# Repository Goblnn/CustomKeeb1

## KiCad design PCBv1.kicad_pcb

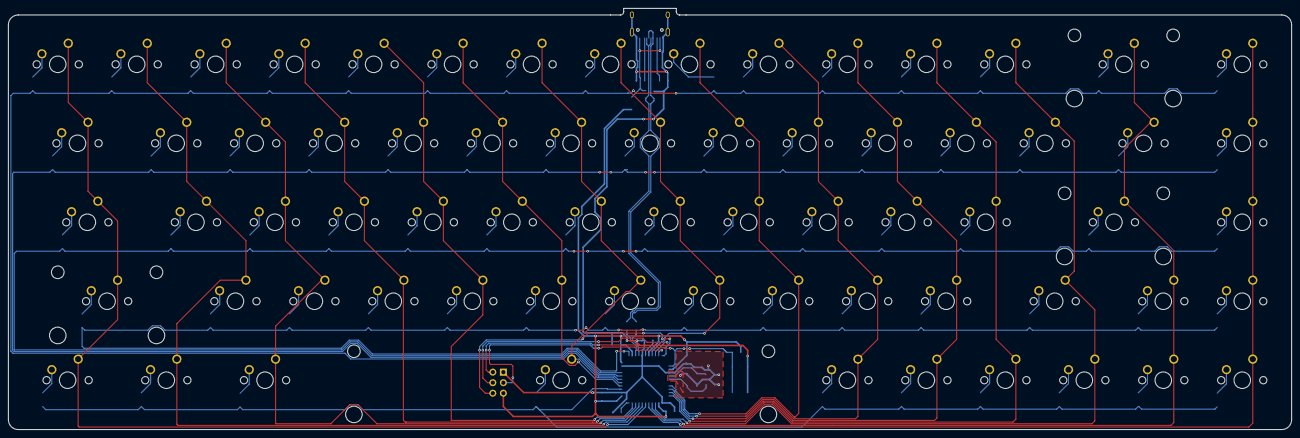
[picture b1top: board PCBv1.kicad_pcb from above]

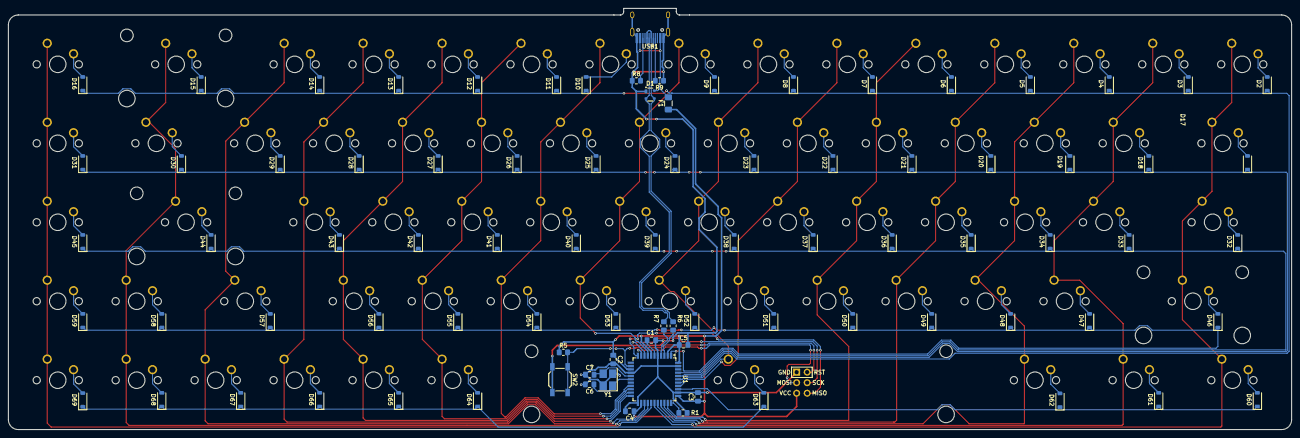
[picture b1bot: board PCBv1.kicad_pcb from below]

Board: 2 copper layers, 309.6 x 101.6 mm, 156 parts (88 on the bottom side), 105 nets.

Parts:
C1: 1uF; C_0805_2012Metric_Pad1.18x1.45mm_HandSolder
C2, C3, C4: 0.1uF; C_0805_2012Metric_Pad1.18x1.45mm_HandSolder
C5: 10uF; C_0805_2012Metric_Pad1.18x1.45mm_HandSolder
C6, C7: 22pF; C_0805_2012Metric_Pad1.18x1.45mm_HandSolder
D1: PRTR5V0U2X; SOT-143
D2, D3, D4, D5, D6, D7, D8, D9, D10, D11, D12, D13, D14, D15, D16, D17, D18, D19, D20, D21, D22, D23, D24, D25, D26, D27, D28, D29, D30, D31, D32, D33, D34, D35, D36, D37, D38, D39, D40, D41, D42, D43, D44, D45, D46, D47, D48, D49, D50, D51, D52, D53, D54, D55, D56, D57, D58, D59, D60, D61, D62, D63, D64, D65, D66, D67, D68, D69: D; D_SOD-123
F1: 500m; Fuse_1206_3216Metric_Pad1.42x1.75mm_HandSolder
J1: AVR-ISP-6; Reset_Pretty-Mask
R1, R5: 10k; R_0805_2012Metric_Pad1.20x1.40mm_HandSolder
R6, R7: 22; R_0805_2012Metric_Pad1.20x1.40mm_HandSolder
R8, R9: 5.1k; R_0805_2012Metric_Pad1.20x1.40mm_HandSolder
SW1: `~; MXOnly-1U-NoLED
SW2: SW_Push_Reset; SW_SPST_SKQG_WithStem
SW3: #1; MXOnly-1U-NoLED
SW4: #2; MXOnly-1U-NoLED
SW5: #3; MXOnly-1U-NoLED
SW6: #4; MXOnly-1U-NoLED
SW7: #5; MXOnly-1U-NoLED
SW8: #6; MXOnly-1U-NoLED
SW9: #7; MXOnly-1U-NoLED
SW10: #8; MXOnly-1U-NoLED
SW11: #9; MXOnly-1U-NoLED
SW12: #0; MXOnly-1U-NoLED
SW13: -_; MXOnly-1U-NoLED
SW14: =+; MXOnly-1U-NoLED
SW15: BSPC; MXOnly-2U-NoLED
SW16: PAUSE; MXOnly-1U-NoLED
SW17: TAB; MXOnly-1.5U-NoLED
SW18: Q; MXOnly-1U-NoLED
SW19: W; MXOnly-1U-NoLED
SW20: E; MXOnly-1U-NoLED
SW21: R; MXOnly-1U-NoLED
SW22: T; MXOnly-1U-NoLED
SW23: Y; MXOnly-1U-NoLED
SW24: U; MXOnly-1U-NoLED
SW25: I; MXOnly-1U-NoLED
SW26: O; MXOnly-1U-NoLED
SW27: P; MXOnly-1U-NoLED
SW28: [{; MXOnly-1U-NoLED
SW29: ]}; MXOnly-1U-NoLED
SW30: \|; MXOnly-1.5U-NoLED
SW31: NEXT; MXOnly-1U-NoLED
SW32: CPSLCK; MXOnly-1.75U-NoLED
SW33: A; MXOnly-1U-NoLED
SW34: S; MXOnly-1U-NoLED
SW35: D; MXOnly-1U-NoLED
SW36: F; MXOnly-1U-NoLED
SW37: G; MXOnly-1U-NoLED
SW38: H; MXOnly-1U-NoLED
SW39: J; MXOnly-1U-NoLED
SW40: K; MXOnly-1U-NoLED
SW41: L; MXOnly-1U-NoLED
SW42: ;:; MXOnly-1U-NoLED
SW43: '"; MXOnly-1U-NoLED
SW44: ENTR; MXOnly-2.25U-NoLED
SW45: PRVS; MXOnly-1U-NoLED
SW46: SHFT; MXOnly-2.25U-NoLED
SW47: Z; MXOnly-1U-NoLED
SW48: X; MXOnly-1U-NoLED
SW49: C; MXOnly-1U-NoLED
SW50: V; MXOnly-1U-NoLED
SW51: B; MXOnly-1U-NoLED
SW52: N; MXOnly-1U-NoLED
SW53: M; MXOnly-1U-NoLED
SW54: ,<; MXOnly-1U-NoLED
SW55: .>; MXOnly-1U-NoLED
SW56: /?; MXOnly-1U-NoLED
SW57: SHFT; MXOnly-1.75U-NoLED
SW58: UP; MXOnly-1U-NoLED
SW59: DEL; MXOnly-1U-NoLED
SW60: CTRL; MXOnly-1.25U-NoLED
SW61: WIN; MXOnly-1.25U-NoLED
SW62: ALT; MXOnly-1.25U-NoLED
SW63: SPC; MXOnly-6.25U-NoLED
SW64: ALT; MXOnly-1U-NoLED
SW65: FN; MXOnly-1U-NoLED
SW66: CTRL; MXOnly-1U-NoLED
SW67: LEFT; MXOnly-1U-NoLED
SW68: DOWN; MXOnly-1U-NoLED
SW69: RIGHT; MXOnly-1U-NoLED
U1: ATmega32U4-A; TQFP-44_10x10mm_P0.8mm
USB1: HRO-TYPE-C-31-M-12; HRO-TYPE-C-31-M-12-HandSoldering
Y1: 16MHz; Crystal_SMD_3225-4Pin_3.2x2.5mm_HandSoldering

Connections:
+5V: C2.1, C3.1, C4.1, C5.1, F1.1, J1.2 (VCC), R5.1, U1.2 (UVCC), U1.7 (VBUS), U1.14 (VCC), U1.24 (AVCC), U1.34 (VCC), U1.44 (AVCC)
D+: R7.2, U1.4 (D+)
D-: R6.2, U1.3 (D-)
DN: D1.3 (I/O2), R6.1, USB1.5 (DN2), USB1.7 (DN1)
DP: D1.2 (I/O1), R7.1, USB1.6 (DP1), USB1.8 (DP2)
GND: C1.2, C2.2, C3.2, C4.2, C5.2, C6.1, C7.1, D1.1 (GND), J1.6 (GND), R1.2, R8.1, R9.1, SW2.2, U1.5 (UGND), U1.15 (GND), U1.23 (GND), U1.35 (GND), U1.43 (GND), USB1.1 (GND), USB1.12 (GND), USB1.13 (SHIELD), Y1.2, Y1.4
MISO: J1.1 (MISO), U1.11 (PB3)
MOSI: J1.4 (MOSI), U1.10 (PB2)
unnamed: D2.2 (A), SW1.1
unnamed: D3.2 (A), SW3.1
unnamed: D4.2 (A), SW4.1
unnamed: D5.2 (A), SW5.1
unnamed: D6.2 (A), SW6.1
unnamed: D7.2 (A), SW7.1
unnamed: D8.2 (A), SW8.1
unnamed: D9.2 (A), SW9.1
unnamed: D10.2 (A), SW10.1
unnamed: D11.2 (A), SW11.1
unnamed: D12.2 (A), SW12.1
unnamed: D13.2 (A), SW13.1
unnamed: D14.2 (A), SW14.1
unnamed: D15.2 (A), SW15.1
unnamed: D16.2 (A), SW16.1
unnamed: D17.2 (A), SW17.1
unnamed: D18.2 (A), SW18.1
unnamed: D19.2 (A), SW19.1
unnamed: D20.2 (A), SW20.1
unnamed: D21.2 (A), SW21.1
unnamed: D22.2 (A), SW22.1
unnamed: D23.2 (A), SW23.1
unnamed: D24.2 (A), SW24.1
unnamed: D25.2 (A), SW25.1
unnamed: D26.2 (A), SW26.1
unnamed: D27.2 (A), SW27.1
unnamed: D28.2 (A), SW28.1
unnamed: D29.2 (A), SW29.1
unnamed: D30.2 (A), SW30.1
unnamed: D31.2 (A), SW31.1
unnamed: D32.2 (A), SW32.1
unnamed: D33.2 (A), SW33.1
unnamed: D34.2 (A), SW34.1
unnamed: D35.2 (A), SW35.1
unnamed: D36.2 (A), SW36.1
unnamed: D37.2 (A), SW37.1
unnamed: D38.2 (A), SW38.1
unnamed: D39.2 (A), SW39.1
unnamed: D40.2 (A), SW40.1
unnamed: D41.2 (A), SW41.1
unnamed: D42.2 (A), SW42.1
unnamed: D43.2 (A), SW43.1
unnamed: D44.2 (A), SW44.1
unnamed: D45.2 (A), SW45.1
unnamed: D46.2 (A), SW46.1
unnamed: D47.2 (A), SW47.1
unnamed: D48.2 (A), SW48.1
unnamed: D49.2 (A), SW49.1
unnamed: D50.2 (A), SW50.1
unnamed: D51.2 (A), SW51.1
unnamed: D52.2 (A), SW52.1
unnamed: D53.2 (A), SW53.1
unnamed: D54.2 (A), SW54.1
unnamed: D55.2 (A), SW55.1
unnamed: D56.2 (A), SW56.1
unnamed: D57.2 (A), SW57.1
unnamed: D58.2 (A), SW58.1
unnamed: D59.2 (A), SW59.1
unnamed: D60.2 (A), SW60.1
unnamed: D61.2 (A), SW61.1
unnamed: D62.2 (A), SW62.1
unnamed: D63.2 (A), SW63.1
unnamed: D64.2 (A), SW64.1
unnamed: D65.2 (A), SW65.1
unnamed: D66.2 (A), SW66.1
unnamed: D67.2 (A), SW67.1
unnamed: D68.2 (A), SW68.1
unnamed: D69.2 (A), SW69.1
unnamed: C1.1, U1.6 (UCAP)
unnamed: C6.2, U1.17 (XTAL1), Y1.1
unnamed: C7.2, U1.16 (XTAL2), Y1.3
unnamed: R1.1, U1.33 (~HWB/PE2)
unnamed: R9.2, USB1.4 (CC1)
unnamed: R8.2, USB1.10 (CC2)
RESET: J1.5 (~RST), R5.2, SW2.1, U1.13 (~RESET)
SCK: J1.3 (SCK), U1.9 (PB1)
VCC: D1.4 (VCC), F1.2, USB1.2 (VBUS), USB1.11 (VBUS)
col0: SW1.2, SW17.2, SW32.2, SW46.2, SW60.2, U1.28 (PB4)
col1: SW3.2, SW18.2, SW33.2, SW47.2, SW61.2, U1.29 (PB5)
col2: SW4.2, SW19.2, SW34.2, SW48.2, SW62.2, U1.30 (PB6)
col3: SW5.2, SW20.2, SW35.2, SW49.2, U1.31 (PC6)
col4: SW6.2, SW21.2, SW36.2, SW50.2, U1.32 (PC7)
col5: SW7.2, SW22.2, SW37.2, SW51.2, U1.37 (PF6)
col6: SW8.2, SW23.2, SW38.2, SW52.2, SW63.2, U1.38 (PF5)
col7: SW9.2, SW24.2, SW39.2, SW53.2, U1.8 (PB0)
col8: SW10.2, SW25.2, SW40.2, SW54.2, U1.19 (PD1)
col9: SW11.2, SW26.2, SW41.2, SW55.2, SW64.2, U1.20 (PD2)
col10: SW12.2, SW27.2, SW42.2, SW56.2, SW65.2, U1.21 (PD3)
col11: SW13.2, SW28.2, SW43.2, SW66.2, U1.22 (PD5)
col12: SW14.2, SW29.2, SW57.2, SW67.2, U1.25 (PD4)
col13: SW15.2, SW30.2, SW44.2, SW58.2, SW68.2, U1.26 (PD6)
col14: SW16.2, SW31.2, SW45.2, SW59.2, SW69.2, U1.27 (PD7)
row0: D2.1 (K), D3.1 (K), D4.1 (K), D5.1 (K), D6.1 (K), D7.1 (K), D8.1 (K), D9.1 (K), D10.1 (K), D11.1 (K), D12.1 (K), D13.1 (K), D14.1 (K), D15.1 (K), D16.1 (K), U1.39 (PF4)
row1: D17.1 (K), D18.1 (K), D19.1 (K), D20.1 (K), D21.1 (K), D22.1 (K), D23.1 (K), D24.1 (K), D25.1 (K), D26.1 (K), D27.1 (K), D28.1 (K), D29.1 (K), D30.1 (K), D31.1 (K), U1.40 (PF1)
row2: D32.1 (K), D33.1 (K), D34.1 (K), D35.1 (K), D36.1 (K), D37.1 (K), D38.1 (K), D39.1 (K), D40.1 (K), D41.1 (K), D42.1 (K), D43.1 (K), D44.1 (K), D45.1 (K), U1.41 (PF0)
row3: D46.1 (K), D47.1 (K), D48.1 (K), D49.1 (K), D50.1 (K), D51.1 (K), D52.1 (K), D53.1 (K), D54.1 (K), D55.1 (K), D56.1 (K), D57.1 (K), D58.1 (K), D59.1 (K), U1.1 (PE6)
row4: D60.1 (K), D61.1 (K), D62.1 (K), D63.1 (K), D64.1 (K), D65.1 (K), D66.1 (K), D67.1 (K), D68.1 (K), D69.1 (K), U1.36 (PF7)

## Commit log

2025-04-17 rarw
2025-04-17 Add submodules
2025-04-17 adas
2025-04-17 preogress
2025-04-19 asjkdhnasjkd
2025-04-19 styuif
2025-04-19 rah stuff
2025-04-19 some progress
2025-04-19 pcb start
2025-04-20 maybe done but probs not
2025-04-20 more done
2025-04-20 small fixes
2025-04-21 asdasd
